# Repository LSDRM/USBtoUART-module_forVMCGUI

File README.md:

# USBtoUART-module_forVMCGUI
Electronic board files for USB to UART module. Has been developed for VMCGUI, but feel free to use it with any other system. The boards has been drawn under KiCad 5.1.0

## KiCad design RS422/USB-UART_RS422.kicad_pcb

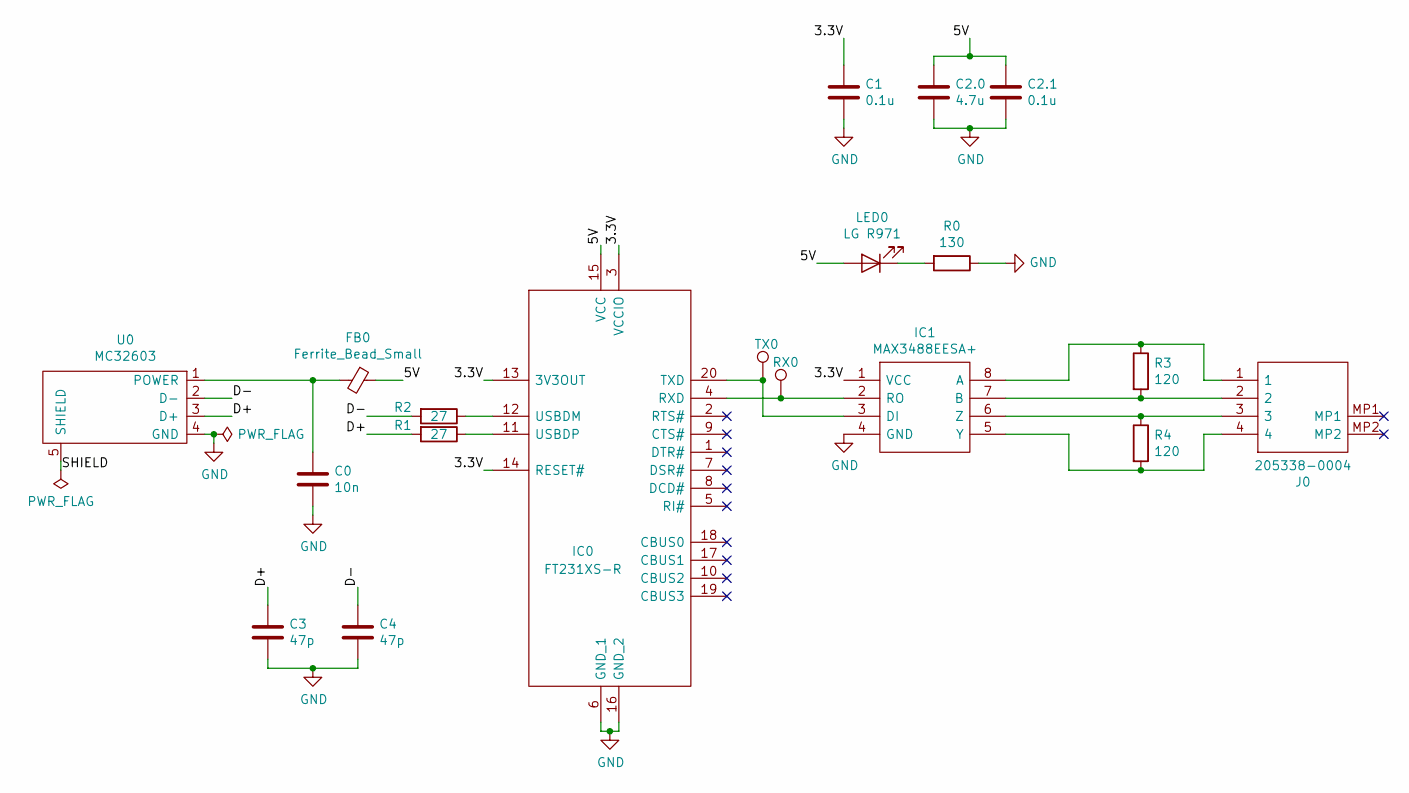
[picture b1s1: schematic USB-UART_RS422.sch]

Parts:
C0: 10n; C_1206_3216Metric_Pad1.33x1.80mm_HandSolder
C1, C2.1: 0.1u; C_0603_1608Metric_Pad1.08x0.95mm_HandSolder
C2.0: 4.7u; C_0603_1608Metric_Pad1.08x0.95mm_HandSolder
C3, C4: 47p; C_0805_2012Metric_Pad1.18x1.45mm_HandSolder
FB0: Ferrite_Bead_Small; L_0805_2012Metric_Pad1.15x1.40mm_HandSolder
IC0: FT231XS-R; SOP64P599X175-20N; Mouser Part Number 895-FT231XS-R
IC1: MAX3488EESA+; SOIC127P600X175-8N; Mouser Part Number 700-MAX3488EESA
J0: 205338-0004; 2053380004; Manufacturer_Part_Number 205338-0004; Mouser Part Number 538-205338-0004
LED0: LG R971; LED_0805_2012Metric_Pad1.15x1.40mm_HandSolder
R0: 130; R_0805_2012Metric_Pad1.20x1.40mm_HandSolder
R1, R2: 27; R_0805_2012Metric_Pad1.20x1.40mm_HandSolder
R3, R4: 120; R_0805_2012Metric_Pad1.20x1.40mm_HandSolder
RX0: TestPoint; TestPoint_THTPad_D2.5mm_Drill1.2mm
TX0: TestPoint; TestPoint_THTPad_D2.5mm_Drill1.2mm
U0: MC32603

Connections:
/3.3V: C1.1, IC0.3 (VCCIO), IC0.13 (3V3OUT), IC0.14 (RESET#), IC1.1 (VCC)
/5V: C2.0.1, C2.1.1, FB0.1, IC0.15 (VCC), LED0.2 (A)
/D+: C3.2, R1.2, U0.3 (D+)
/D-: C4.1, R2.2, U0.2 (D-)
/SHIELD: U0.5 (SHIELD)
GND: C0.2, C1.2, C2.0.2, C2.1.2, C3.1, C4.2, IC0.6 (GND_1), IC0.16 (GND_2), IC1.4 (GND), R0.1, U0.4 (GND)
unnamed: C0.1, FB0.2, U0.1 (POWER)
unnamed: IC0.4 (RXD), IC1.2 (RO), RX0.1
unnamed: IC0.11 (USBDP), R1.1
unnamed: IC0.12 (USBDM), R2.1
unnamed: IC0.20 (TXD), IC1.3 (DI), TX0.1
unnamed: IC1.5 (Y), J0.4, R4.2
unnamed: IC1.6 (Z), J0.3, R4.1
unnamed: IC1.7 (B), J0.2, R3.2
unnamed: IC1.8 (A), J0.1, R3.1
unnamed: LED0.1 (K), R0.2

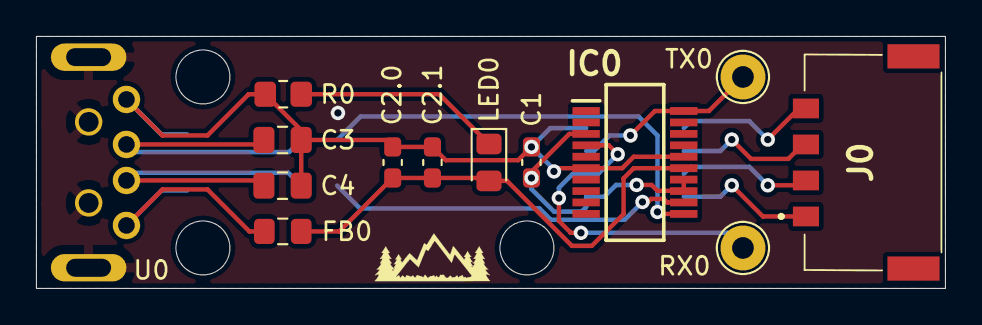
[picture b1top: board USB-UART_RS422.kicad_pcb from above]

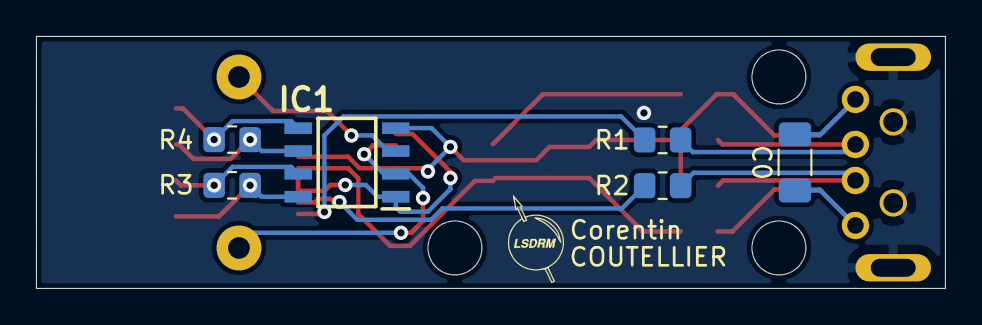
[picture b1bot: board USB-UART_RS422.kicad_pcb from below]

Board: 2 copper layers, 50.5 x 14.0 mm, 19 parts (6 on the bottom side), 15 nets.

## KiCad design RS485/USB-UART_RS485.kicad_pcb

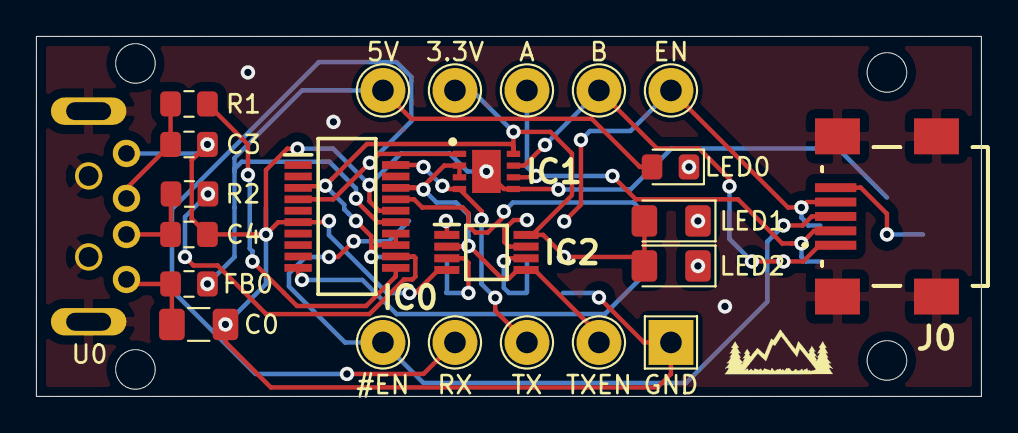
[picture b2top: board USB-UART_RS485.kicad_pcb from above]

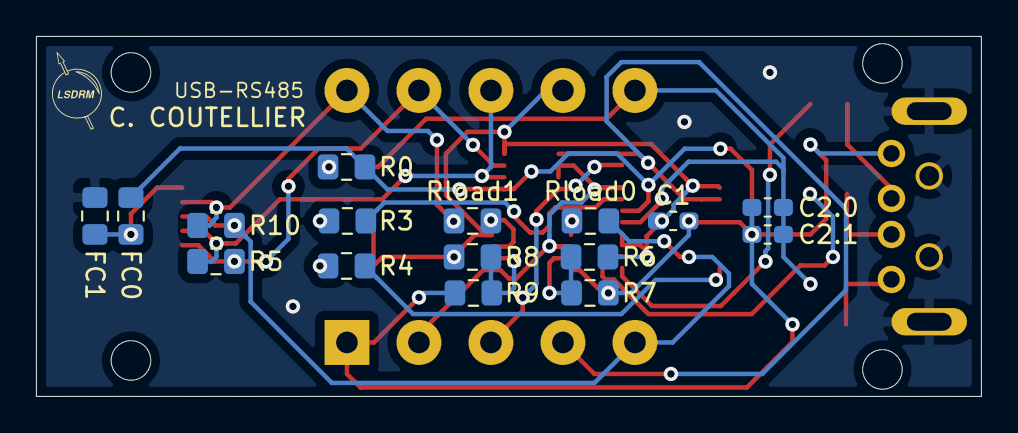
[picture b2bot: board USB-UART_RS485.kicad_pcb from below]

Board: 2 copper layers, 52.5 x 20.0 mm, 39 parts (16 on the bottom side), 26 nets.

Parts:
3.3V, 5V: TestPoint; TestPoint_THTPad_D2.5mm_Drill1.2mm
A: TestPoint; TestPoint_THTPad_D2.5mm_Drill1.2mm
B: TestPoint; TestPoint_THTPad_D2.5mm_Drill1.2mm
C0: 10n; C_1206_3216Metric_Pad1.42x1.75mm_HandSolder
C1, C2.1: 0.1u; C_0603_1608Metric_Pad1.05x0.95mm_HandSolder
C2.0: 4.7u; C_0603_1608Metric_Pad1.05x0.95mm_HandSolder
C3, C4: 47p; C_0805_2012Metric_Pad1.15x1.40mm_HandSolder
EN: TestPoint; TestPoint_THTPad_D2.5mm_Drill1.2mm
FB0: Ferrite_Bead_Small; L_0805_2012Metric_Pad1.15x1.40mm_HandSolder
FC0, FC1: R; R_0805_2012Metric_Pad1.15x1.40mm_HandSolder
GND: TestPoint; TestPoint_THTPad_2.5x2.5mm_Drill1.2mm
IC0: FT231XS-R; SOP64P599X175-20N
IC1: MAX14840EATA+; SON65P300X300X80-9N
IC2: NCS20032DMR2G; SOP65P490X110-8N
J0: USB2066-05-RBHM-15-STB-00-00-A; USB206605RBHM15STB0000A
LED0: LG R971; LED_0805_2012Metric_Pad1.15x1.40mm_HandSolder
LED1, LED2: KP-3216SURC; LED_1206_3216Metric_Pad1.42x1.75mm_HandSolder
R0: 130; R_0805_2012Metric_Pad1.15x1.40mm_HandSolder
R1, R2: 27; R_0805_2012Metric_Pad1.15x1.40mm_HandSolder
R3, R4: 68; R_0805_2012Metric_Pad1.15x1.40mm_HandSolder
R5, R10: 120; R_0805_2012Metric_Pad1.15x1.40mm_HandSolder
R6, R7, R8, R9: 1M; R_0805_2012Metric_Pad1.15x1.40mm_HandSolder
RX: TestPoint; TestPoint_THTPad_D2.5mm_Drill1.2mm
Rload0, Rload1: 10k; R_0805_2012Metric_Pad1.15x1.40mm_HandSolder
TX: TestPoint; TestPoint_THTPad_D2.5mm_Drill1.2mm
TXEN: TestPoint; TestPoint_THTPad_D2.5mm_Drill1.2mm
U0: MC32603

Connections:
/3.3V: 3.3V.1, C1.1, IC0.3, IC0.13, IC0.14, IC1.8, IC2.8, LED1.2, LED2.2, R6.2, R8.1
/5V: 5V.1, C2.0.1, C2.1.1, FB0.1, IC0.15, LED0.2
/#ENABLE: J0.3, R10.1, Rload0.2
/D+: C3.2, R1.2, U0.3
/D-: C4.1, R2.2, U0.2
/ENABLE: EN.1, J0.4, R10.2, Rload1.1
/SHIELD: FC1.2, J0.MP1, J0.MP2, J0.MP3, J0.MP4, U0.5
/TXDEN: IC0.18, IC1.2, IC1.3, IC2.2, IC2.5, TXEN.1
GND: C0.2, C1.2, C2.0.2, C2.1.2, C3.1, C4.2, FC0.2, GND.1, IC0.6, IC0.16, IC1.5, IC1.9, IC2.4, R0.1, R7.2, R9.2, U0.4
unnamed: A.1, IC1.6, J0.2, R5.2
unnamed: B.1, IC1.7, J0.1, R5.1
unnamed: C0.1, FB0.2, U0.1
unnamed: FC0.1, FC1.1, J0.5
unnamed: IC0.4, IC1.1, RX.1
unnamed: IC0.10, R4.1
unnamed: IC0.11, R1.1
unnamed: IC0.12, R2.1
unnamed: IC0.17, R3.1
unnamed: IC0.20, IC1.4, TX.1
unnamed: IC2.1, Rload0.1
unnamed: IC2.3, R6.1, R7.1
unnamed: IC2.6, R8.2, R9.1
unnamed: IC2.7, Rload1.2
unnamed: LED0.1, R0.2
unnamed: LED1.1, R3.2
unnamed: LED2.1, R4.2
